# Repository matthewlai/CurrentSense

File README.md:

# CurrentSense
Current sense amplifier board

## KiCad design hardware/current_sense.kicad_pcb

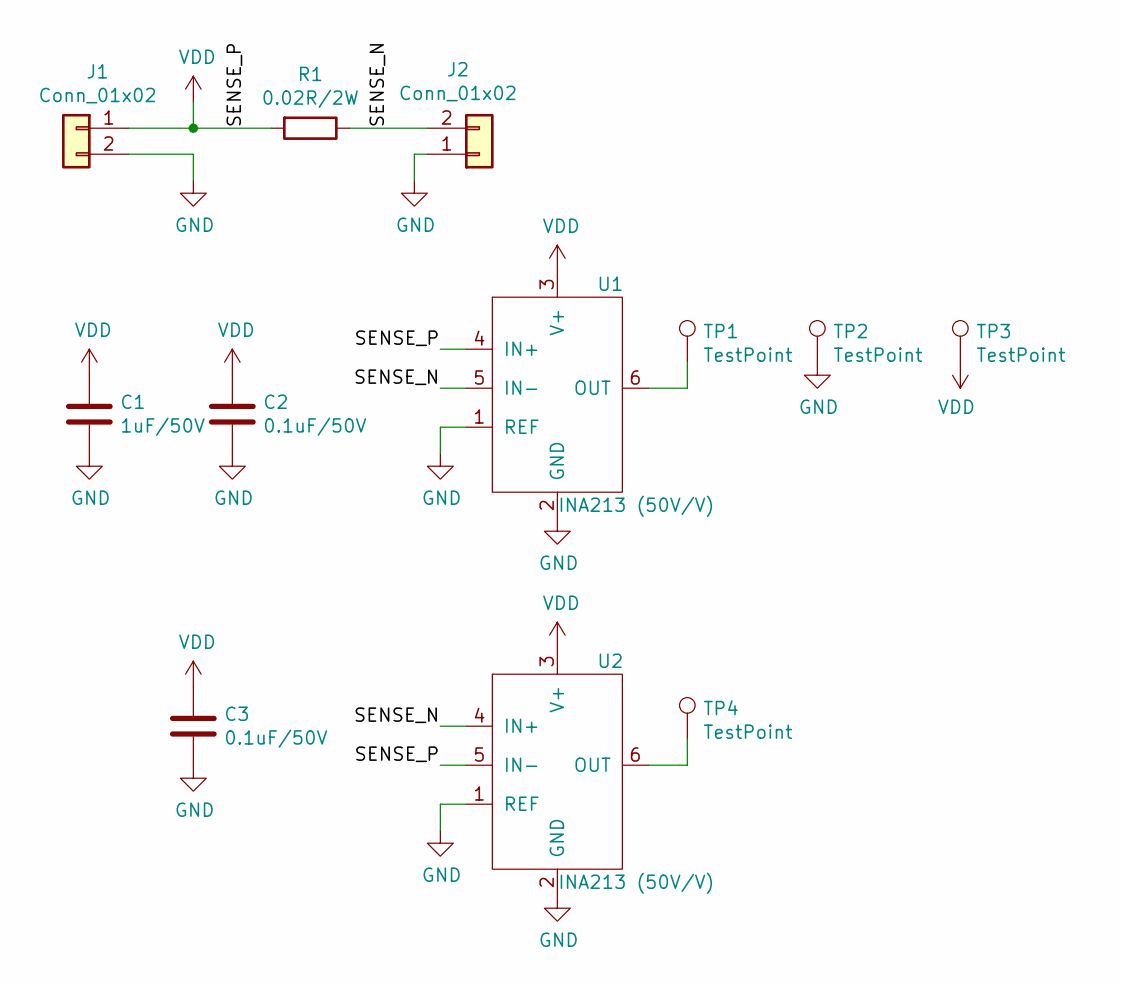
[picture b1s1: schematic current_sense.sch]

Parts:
C1: 1uF/50V; R_0603_1608Metric; LCSC C15849
C2, C3: 0.1uF/50V; R_0603_1608Metric; LCSC C14663
J1, J2: Conn_01x02; TerminalBlock_Phoenix_MKDS-3-2-5.08_1x02_P5.08mm_Horizontal
R1: 0.02R/2W; R_2512_6332Metric; LCSC C68608
TP1, TP2, TP3, TP4: TestPoint; TestPoint_Loop_D3.50mm_Drill1.4mm_Beaded
U1, U2: INA213 (50V/V); SOT-363_SC-70-6; LCSC C129346

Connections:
/SENSE_N: J2.2, R1.1, U1.5 (IN-), U2.4 (IN+)
GND: C1.2, C2.2, C3.2, J1.2, J2.1, TP2.1, U1.1 (REF), U1.2 (GND), U2.1 (REF), U2.2 (GND)
unnamed: TP1.1, U1.6 (OUT)
unnamed: TP4.1, U2.6 (OUT)
VDD: C1.1, C2.1, C3.1, J1.1, R1.2, TP3.1, U1.3 (V+), U1.4 (IN+), U2.3 (V+), U2.5 (IN-)

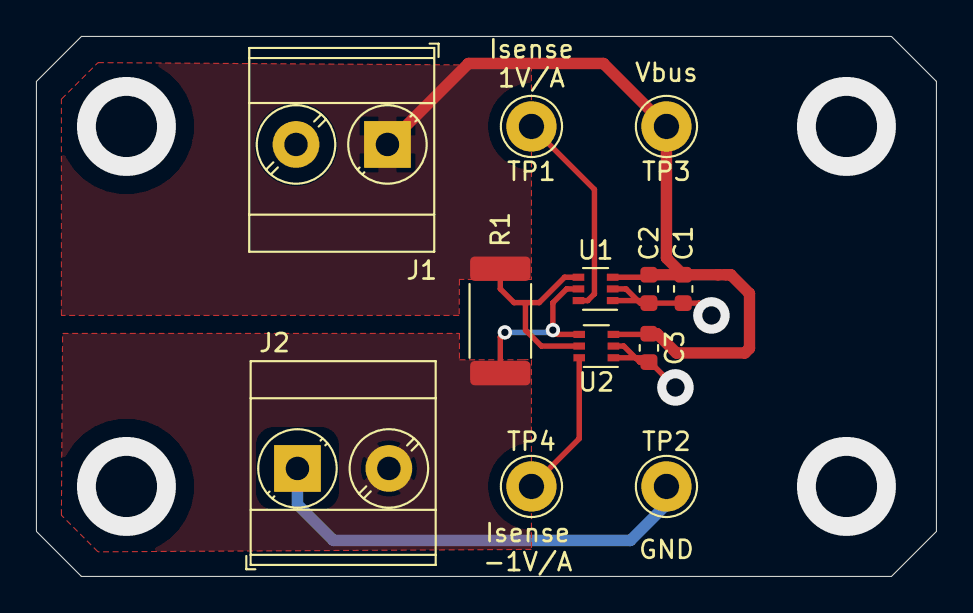
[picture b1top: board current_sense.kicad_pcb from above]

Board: 2 copper layers, 50.0 x 30.0 mm, 12 parts (0 on the bottom side), 5 nets.

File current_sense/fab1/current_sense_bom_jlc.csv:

"Comment","Designator","Footprint","LCSC Part #"
"1uF/50V","C1","R_0603_1608Metric","C15849"
"0.1uF/50V","C2,C3","R_0603_1608Metric","C14663"
"0.02R/2W","R1","R_2512_6332Metric","C68608"
"INA213 (50V/V)","U1,U2","SOT-363_SC-70-6","C129346"

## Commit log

2020-08-04 First hardware version
2020-08-13 Updated silkscreen, removed archive
2020-08-13 Directory re-org, and added SMT placement files
2020-08-13 Added SMT fab files
2020-08-13 Updated license
2020-08-13 Updated silkscreen
